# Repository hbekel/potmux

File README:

PotMux -- Hardware add-on to reroute C64 control port pot lines
(C) 2020 Henning Liebenau <henning.liebenau@protonmail.com>

This project is currently in early beta state and things may
change without notice.

The PotMux is a small hardware add-on for the C64 that allows the user
to optionally route the control port potentiometer lines to a
destination other than the SID. It is mainly intended to be used with
the Keyman64 for the purpose of mapping additional joystick buttons
connected to the potentiometer lines to user defined keystrokes.

For details about the hardware, see ./hardware/README.txt

The potmux utility contained in this archive can be used to prefix an
existing C64 program with a specific potmux configuration for the
Keyman64. The resulting program will first configure the Keyman64
using its serial interface connected to the tapeport lines "Cassette
Sense" and "Cassette Data" and then run the original program.

Usage: potmux [<option>...] <program> [<button|switch>...]

Options:
         -h, --help           : print this help text
         -v, --version        : print version information
         -o, --outfile <file> : output file (default: stdout)

Arguments:
         <program> : C64 program file to patch
         <button>  : route a joystick button to a key
         <switch>  : specify enable line and state

Example:
         potmux -o patched.prg game.prg a0:on b1:space

Assuming that the PotMux EN line is connected to the keyman line on
port a bit 0, the "a0:on" switch specification assures that the potmux
will be enabled by pulling that line low. And assuming that one of the
PotMux button output lines is connected to the keyman control line on
port b bit 1, the "b1:space" will configure the keyman to send a space
key press when the corresponding button is pressed.

LICENSING

Hardware and Software licensed under MIT-style licensing schemes

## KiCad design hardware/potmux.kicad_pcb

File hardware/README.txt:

PotMux Rev.2 -- Pot line multiplexer for the C64
Copyright Henning Bekel 2016.
Licensed under CERN OSH v.1.2 (see LICENSE.txt)

In the C64 there is a 4066 IC that selects two of the four analog
lines from the control ports (POTAX, POTAY, POTBX, POTBY) to the two
analog input lines of the SID, depending on the setting of the CIAs
PA6 and PA7 line. This allows the programmer to choose which paddle
pair or mouse to read from the SID by setting the CIA lines
accordingly.

This board replaces the 4066 and adds the ability to alternatively
route the four analog control port lines somewhere else instead.

When the boards enable line (/EN) is high, the control port lines are
routed to the SID as usual, selected by PA6 and PA7.

When /EN is low, the control port lines POTAX, POTAY, POTBX and POTBY
are routed to the pins A1, A2, B1 and B2.

On older C64 mainboards, the 4066 replaced by this board is annotated
with U28. On the newer 250469 revision, the 4066 is annotated with
U18.

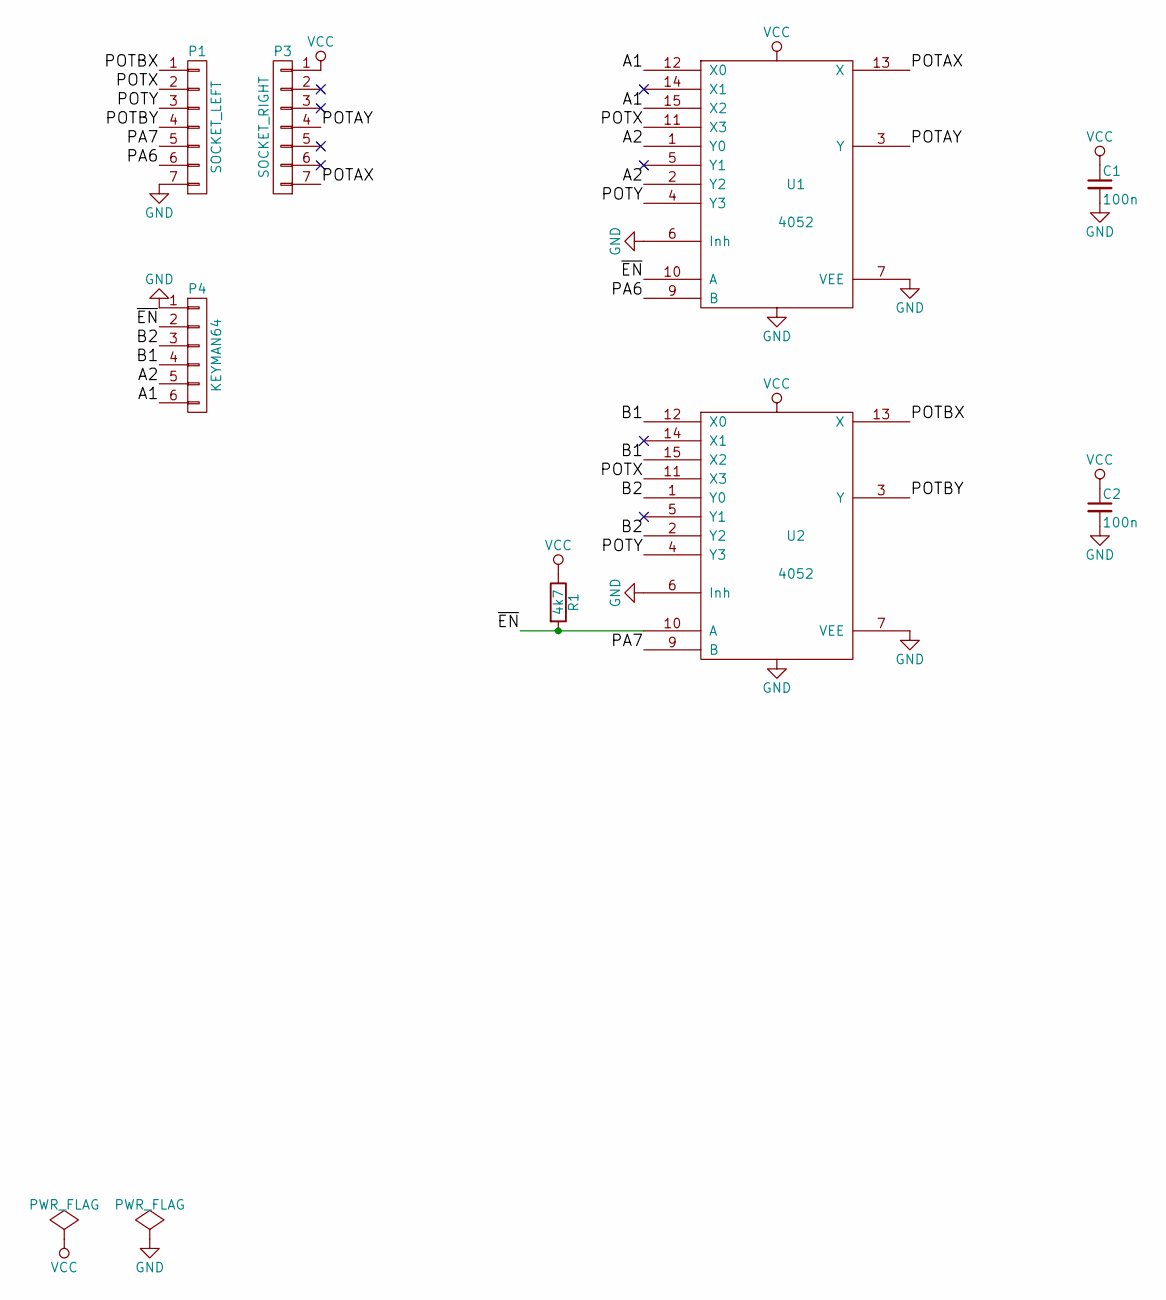
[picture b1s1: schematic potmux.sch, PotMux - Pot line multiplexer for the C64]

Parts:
C1, C2: 100n; C_Disc_D3.0mm_W1.6mm_P2.50mm
P1: SOCKET_LEFT; Pin_Header_Straight_1x07
P3: SOCKET_RIGHT; Pin_Header_Straight_1x07
P4: KEYMAN64; Pin_Header_Angled_1x06_Pitch2.54mm
R1: 4k7; R3
U1, U2: 4052; DIP-16_W7.62mm

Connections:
/A1: P4.6, U1.12 (X0), U1.15 (X2)
/A2: P4.5, U1.1 (Y0), U1.2 (Y2)
/B1: P4.4, U2.12 (X0), U2.15 (X2)
/B2: P4.3, U2.1 (Y0), U2.2 (Y2)
/PA6: P1.6, U1.9 (B)
/PA7: P1.5, U2.9 (B)
/POTAX: P3.7, U1.13 (X)
/POTAY: P3.4, U1.3 (Y)
/POTBX: P1.1, U2.13 (X)
/POTBY: P1.4, U2.3 (Y)
/POTX: P1.2, U1.11 (X3), U2.11 (X3)
/POTY: P1.3, U1.4 (Y3), U2.4 (Y3)
/~EN: P4.2, R1.2, U1.10 (A), U2.10 (A)
GND: C1.2, C2.2, P1.7, P4.1, U1.6 (Inh), U1.7 (VEE), U1.8 (VSS), U2.6 (Inh), U2.7 (VEE), U2.8 (VSS)
VCC: C1.1, C2.1, P3.1, R1.1, U1.16 (VDD), U2.16 (VDD)

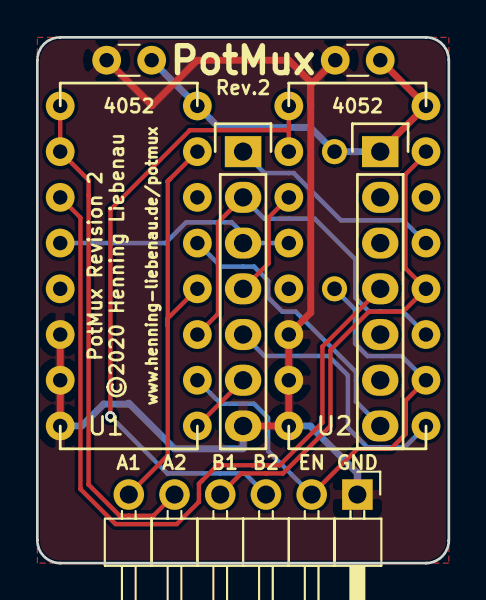
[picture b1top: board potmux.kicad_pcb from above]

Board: 2 copper layers, 22.9 x 29.2 mm, 8 parts (1 on the bottom side), 15 nets.

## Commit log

2016-10-27 Licensed under CERN OHL v.1.2
2016-10-28 Added pdf renderings of schematics and layout, cleaned up
2016-10-28 Added README file
2016-11-01 Cleanups and clarifications, fixed file modes
2016-11-09 Improved README.txt
2016-11-09 Revision 1, added gerber files for production
2017-05-05 Revision 2, updated gerber files for production
    This revision moves the pin header to the bottom.
2017-05-21 Hardware: Moved into hardware directory
2017-05-21 Software: Added sources, readme, license
2017-05-21 Software: Added .gitignore
2017-05-21 Makefile: Added win32 target, using mingw
2017-06-03 Software: Fixed assembly code for KickAssember 3.x
2017-06-03 Makefile: Use KickAssembler from env if defined
2017-06-03 Project: Improved README
2017-06-03 Software: Improved --help text, README
2017-06-23 Hardware: Improved gerber Makefile, updated gerber files
2017-07-24 Adjustments for setting enable line using keyman serial commands
2017-07-24 Avoid mapping buttons to expanded ports
2018-01-01 Improved layout, silk screen
2020-10-07 Changes in preparation for release
    - Changed Licenses to MIT-style licensing schemes
    - Removed files required by cern ohl
    - Rerendered schematic svg
    - Improved silkscreen, updated last name and Copyright notices
    - Adjustments for KiCAD 5.x
    - Improved Makefile
2020-10-07 Corrected README

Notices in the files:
hardware/potmux.kicad_pcb:
This documentation describes Open Hardware and is licensed under the CERN OHL v. 1.2.\
You may redistribute and modify this documentation under the terms of the CERN OHL v.1.2.\
©2020 Henning Liebenau
